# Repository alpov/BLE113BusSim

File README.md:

# BLE113BusSim
Testing framework for Bluegiga BLE113 with MSP432. Provides a method to test Bluetooth Low Energy throughput (Bluegiga BLE113) on MSP432 Launchpad boards (TI MSP-EXP432P401R).

### Required hardware
* CC-Debugger http://www.ti.com/tool/cc-debugger
* MSP-EXP432P401R Launchpads http://www.ti.com/tool/msp-exp432p401r
* Bluegiga BLE113 modules

### Required tools and software
* SmartRF Flash Programmer v1 http://www.ti.com/tool/flash-programmer (v1.12.8)
* Bluegiga Bluetooth Smart Software Stack https://www.silabs.com/products/wireless/bluetooth/bluetooth-smart-modules/Pages/bluegiga-bluetooth-smart-software-stack.aspx (v1.4.2)
* TI Code Composer Studio http://processors.wiki.ti.com/index.php/Download_CCS (v6.2.0.00050)
* MSP432 Driver Library http://www.ti.com/tool/mspdriverlib (v.3.21.00.05)

### Random notes from BLE development
* BLE113 uses UART communication. To achieve the highest possible throughput, use at least 1MBaud.
* Sleep mode needs to be used; otherwise the power consumption is large. Wakeup from sleep is acknowledged with an event, handler needs to wait for it.
* Always wait for response after issuing command to BLE113.
* Connections are very stable after being established, but the connection setup itself is not reliable – gives "Connection Failed to be Established (0x023E)". This is documented in Bluegiga API manual. Solution is to send an acknowledged attribute write after connection; this will either proceed or give 0x023E error. In that case, do a reconnect.
* Support for 8 slaves needs to be enabled in both bgproj (config.xml) and CCS project. Minimum connection interval is 20ms for config of up to 8 slaves; this lowers the maximum achievable throughput.
* To use 20ms connection interval with all 8 slaves, it is necessary to start with longer interval (e.g. 100ms), connect all of them, and then issue an update to 20ms. Otherwise the 7th or 8th slave will connect very late or would not connect at all. Connection interval is not updated right after acknowledgement, it takes several communication intervals.
* With 20ms connection interval, the theoretical maximum write throughput for one node is 20B\*(1/(2\*0.02s))=500B/s. This is because the write packet is limited to 20B and each packet is acknowledged. Large values like 21.1kbit/s from our testing are only achievable with optimal payload distribution – maximum packet length to all slaves simultaneously.
* Nice reading to start with BLE:
  * https://bluegiga.zendesk.com/entries/25053373--REFERENCE-BLE-master-slave-GATT-client-server-and-data-RX-TX-basics
  * https://bluegiga.zendesk.com/entries/22412436--REFERENCE-What-is-the-difference-between-BGScript-BGAPI-and-BGLib
  * https://bluegiga.zendesk.com/entries/23173106--REFERENCE-BLE-module-low-power-and-sleep-modes
  * https://bluegiga.zendesk.com/entries/45890933--REFERENCE-BGAPI-BGLib-Implementation-on-BLE-devices
* Module ble.c provides a basic library for MSP432 to support Bluegiga BLE112/113 modules in UART packet mode. Other support files are from Bluegiga bglib SDK.
* Loading the firmware is possible with CC Debugger. Always use Bluegiga BLE SW Update Tool, not the TI Flash Programmer, as the later one will destroy the license key in BLE113.
* BLE is really suited for very slow communication with negligible throughput. It will perform best for e.g. a sensor, which provides up to 20B of data each ~1 second.

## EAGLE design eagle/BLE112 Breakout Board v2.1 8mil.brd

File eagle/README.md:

# Eagle files for MSP432 breakout boards

* msp432_breakout_ble113 - for BLE113 module
* msp432_breakout_hm10 - for HM-10 module (not tested)
* msp432_breakout_uart - for RS232 and RS485 buses
* ~~msp432_breakout_i2c~~ - for I2C regular and I2C differential buses; warning: the driver footprints are both wrong, need to be fixed before use!
* ~~sf-bluegiga.lbr~~ - library with components; BLE113 is OK, I2C drivers need to be fixed before use!
* BLE112 Breakout Board v2.1 8mil - minor redesign of http://www.inmojo.com/store/jeff-rowberg/item/ble112-bluetooth-low-energy-breakout/ for 8mil DRC; this board with BLE112 can be used as a BLE sniffer, see http://www.ti.com/tool/packet-sniffer

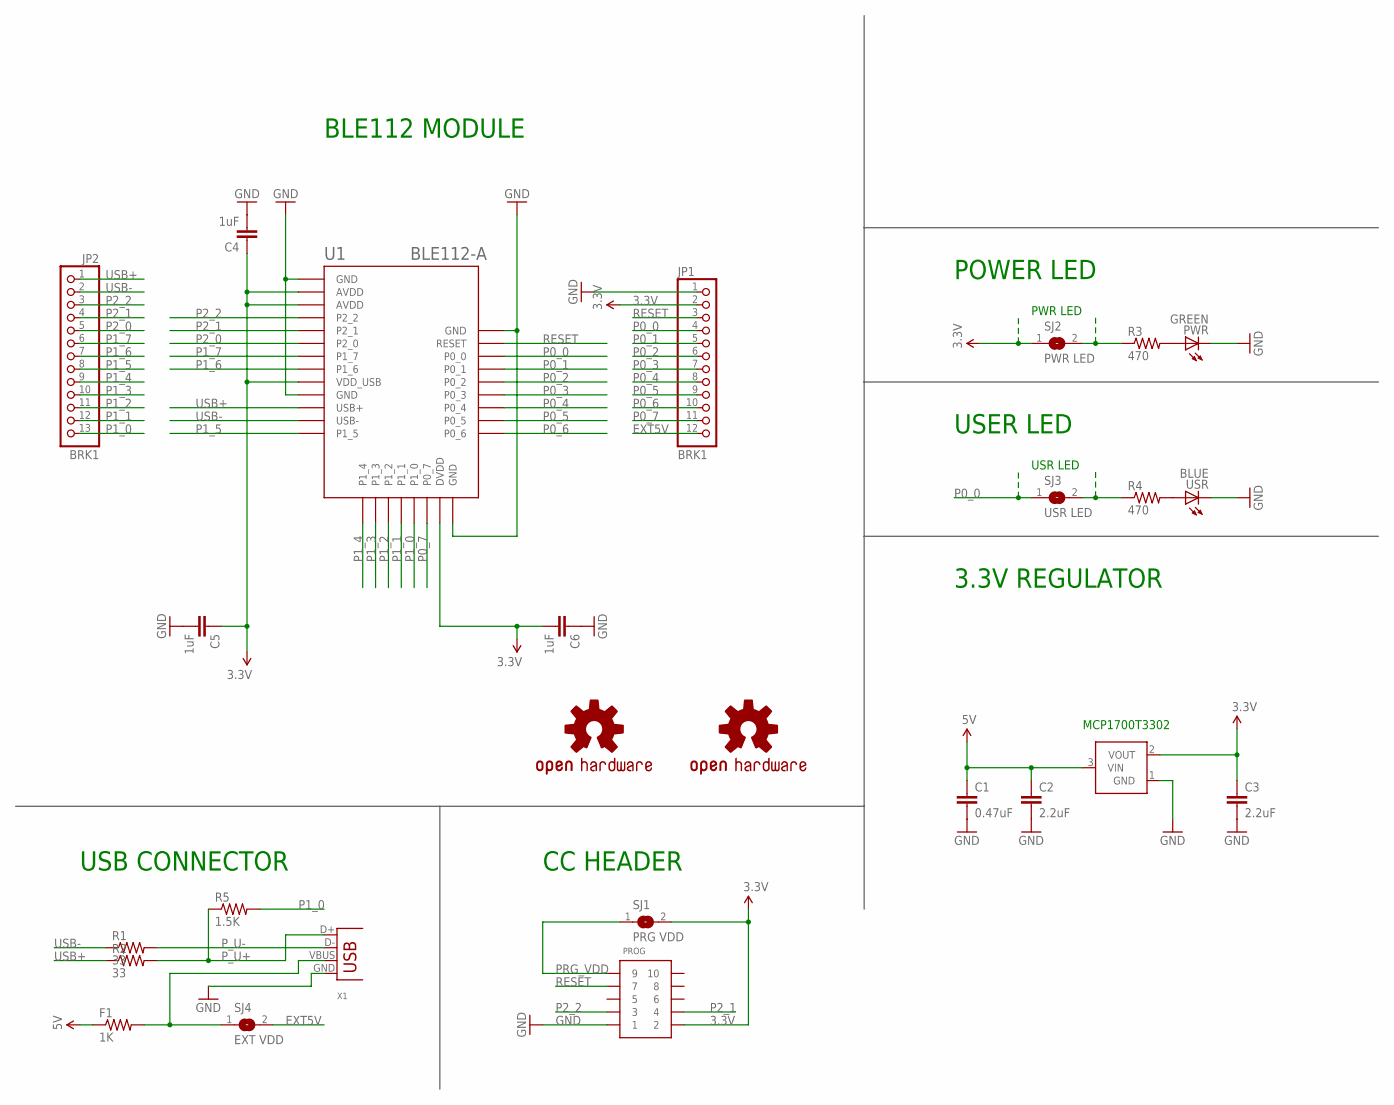
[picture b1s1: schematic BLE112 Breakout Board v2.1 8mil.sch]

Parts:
C1: 0.47uF; 0603-CAP
C2, C3: 2.2uF; 0603-CAP
C4, C5, C6: 1uF; 0603-CAP
F1: 1K; 0805
JP1: BRK1; 1X12
JP2: BRK1; 1X13
OSHW1: OSHW-LOGOL; OSHW-LOGO-L
OSHW2: OSHW-LOGOS; OSHW-LOGO-S
PROG: CONN_5-2-FTSH-V; FTSH-105-DV
PWR: GREEN; CHIPLED_0805
R1, R2: 33; 0603-RES
R3, R4: 470; R0603
R5: 1.5K; 0603-RES
SJ1: PRG VDD; SJ
SJ2: PWR LED; SJ
SJ3: USR LED; SJ
SJ4: EXT VDD; SJ
U1: BLE112-A
U2: MCP1700; SOT23-3
USR: BLUE; CHIPLED_0805
X1: USB-MB-S

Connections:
3.3V: C3.1, C4.1, C5.1, C6.2, JP1.2, PROG.2, SJ1.2, SJ2.1, U1.AVDD1 (AVDD), U1.AVDD2 (AVDD), U1.DVDD, U1.VDD_USB, U2.2 (VOUT)
5V: C1.1, C2.1, F1.1, U2.3 (VIN)
EXT5V: JP1.12, SJ4.2
GND: C1.2, C2.2, C3.2, C4.2, C5.2, C6.1, JP1.1, PROG.1, PWR.C, U1.GND1 (GND), U1.GND2 (GND), U1.GND3 (GND), U1.GND4 (GND), U2.1 (GND), USR.C, X1.GND
unnamed: PWR.A, R3.2
unnamed: R3.1, SJ2.2
unnamed: R4.2, USR.A
unnamed: R4.1, SJ3.2
P0_0: JP1.4, SJ3.1, U1.P0_0
P0_1: JP1.5, U1.P0_1
P0_2: JP1.6, U1.P0_2
P0_3: JP1.7, U1.P0_3
P0_4: JP1.8, U1.P0_4
P0_5: JP1.9, U1.P0_5
P0_6: JP1.10, U1.P0_6
P0_7: JP1.11, U1.P0_7
P1_0: JP2.13, R5.2, U1.P1_0
P1_1: JP2.12, U1.P1_1
P1_2: JP2.11, U1.P1_2
P1_3: JP2.10, U1.P1_3
P1_4: JP2.9, U1.P1_4
P1_5: JP2.8, U1.P1_5
P1_6: JP2.7, U1.P1_6
P1_7: JP2.6, U1.P1_7
P2_0: JP2.5, U1.P2_0
P2_1: JP2.4, PROG.4, U1.P2_1
P2_2: JP2.3, PROG.3, U1.P2_2
PRG_VDD: PROG.9, SJ1.1
P_U+: R2.2, R5.1, X1.D+
P_U-: R1.2, X1.D-
RESET: JP1.3, PROG.7, U1.RESET
USB+: JP2.1, R2.1, U1.USB+
USB-: JP2.2, R1.1, U1.USB-
VBUS: F1.2, SJ4.1, X1.VBUS

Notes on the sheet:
PWR LED
USR LED
POWER LED
USER LED
USB CONNECTOR
CC HEADER
BLE112 MODULE
3.3V REGULATOR
MCP1700T3302

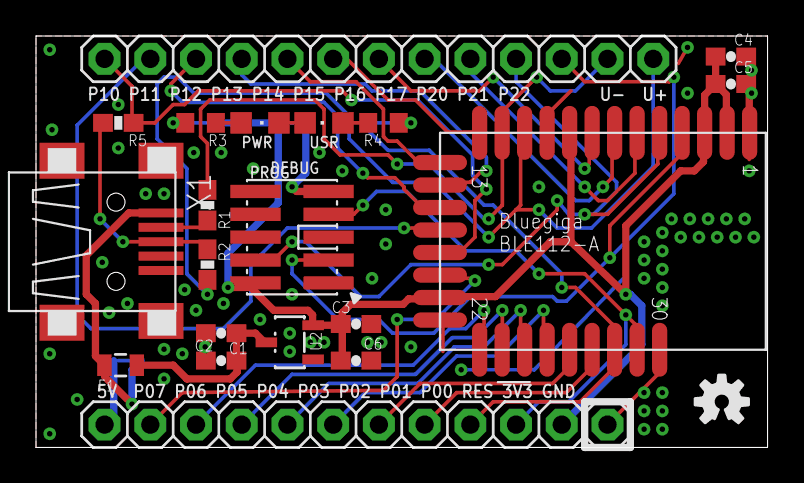
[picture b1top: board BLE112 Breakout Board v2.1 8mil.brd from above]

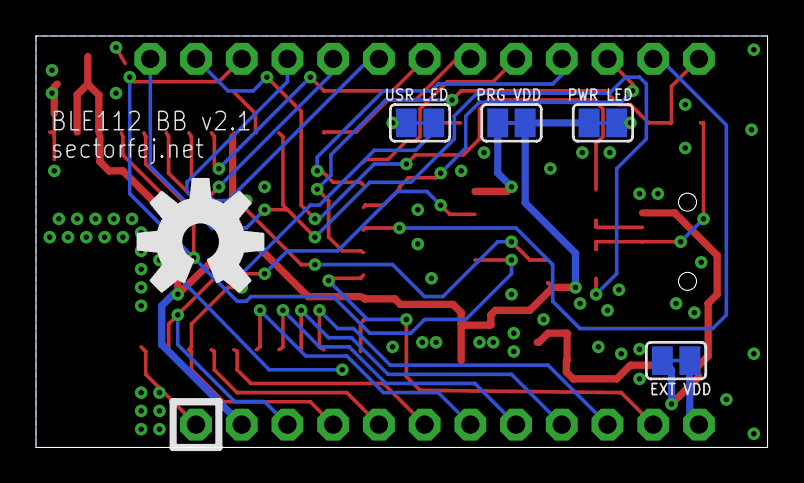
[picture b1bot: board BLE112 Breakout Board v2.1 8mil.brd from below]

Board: 2 copper layers, 40.6 x 22.9 mm, 26 parts (5 on the bottom side), 34 nets.

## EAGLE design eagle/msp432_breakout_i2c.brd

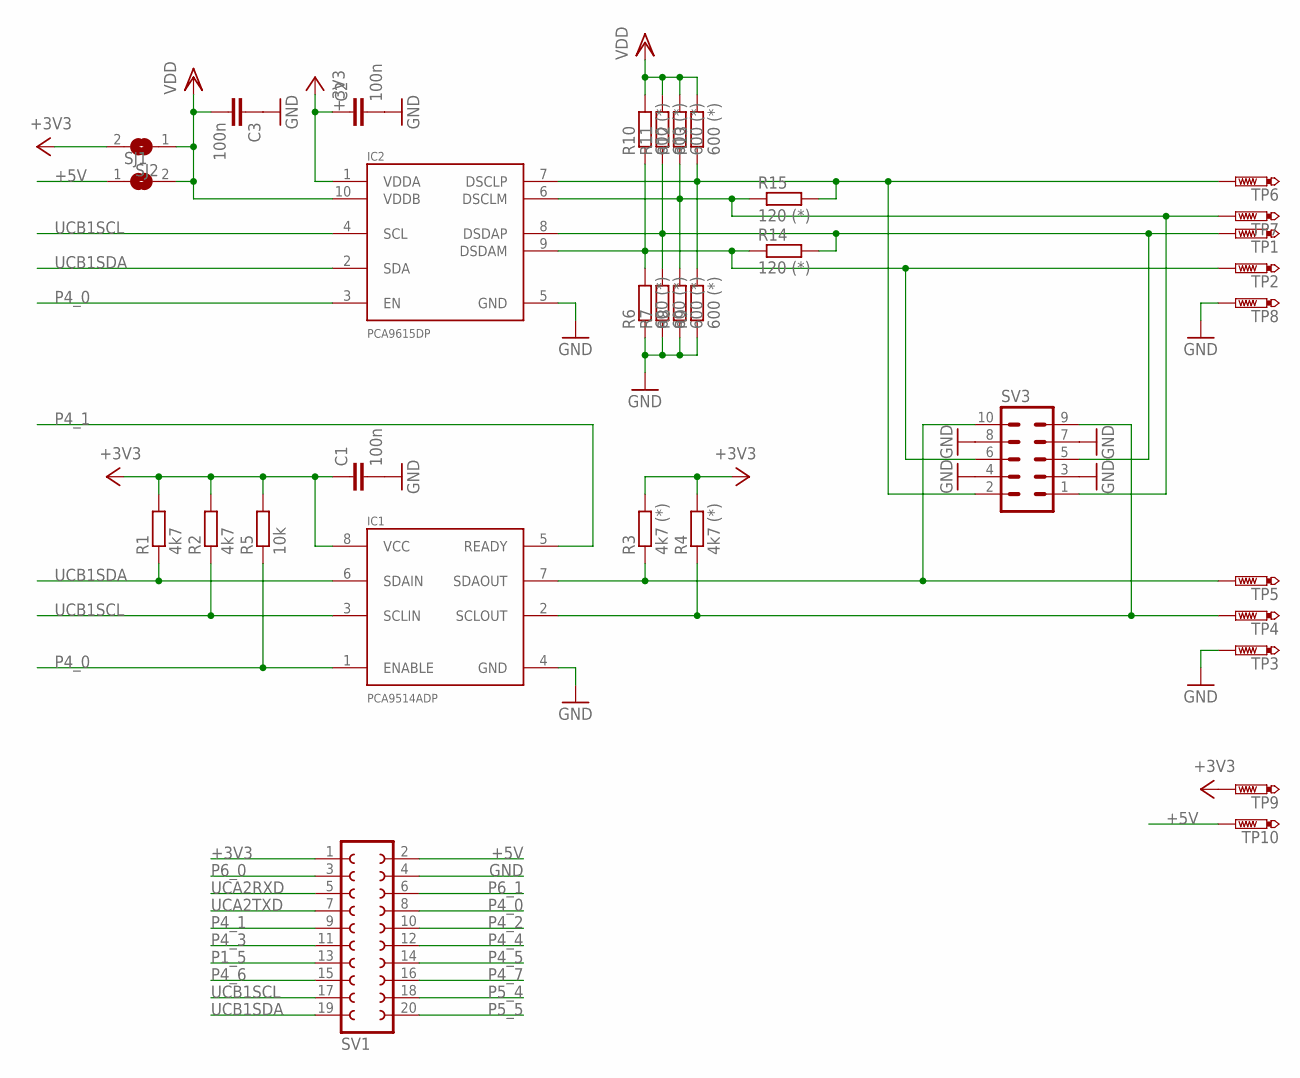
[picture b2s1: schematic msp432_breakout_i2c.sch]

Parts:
C1, C2, C3: 100n; C0603
IC1: PCA9514ADP; TSSOP8
IC2: PCA9615DP; TSSOP10
R1, R2: 4k7; R0603
R3, R4: 4k7 (*); R0603
R5: 10k; R0603
R6, R7, R8, R9, R10, R11, R12, R13: 600 (*); R0603
R14, R15: 120 (*); R0603
SJ1, SJ2: SJ
SV1: FE10-2
SV3: ML10
TP1: DSDAP; P1-17
TP2: DSDAM; P1-17
TP3, TP8: GND; P1-17
TP4: SCLOUT; P1-17
TP5: SDAOUT; P1-17
TP6: DSCLP; P1-17
TP7: DSCLM; P1-17
TP9: 3V3; P1-17
TP10: 5V; P1-17

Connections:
+3V3: C1.1, C2.1, IC1.8 (VCC), IC2.1 (VDDA), R1.2, R2.2, R3.2, R4.2, R5.2, SJ2.2, SV1.1, TP9.TP
+5V: SJ1.1, SV1.2, TP10.TP
GND: C1.2, C2.2, C3.1, IC1.4 (GND), IC2.5 (GND), R6.1, R7.1, R8.1, R9.1, SV1.4, SV3.3, SV3.4, SV3.7, SV3.8, TP3.TP, TP8.TP
P1_5: SV1.13
P4_0: IC1.1 (ENABLE), IC2.3 (EN), R5.1, SV1.8
P4_1: IC1.5 (READY), SV1.9
P4_2: SV1.10
P4_3: SV1.11
P4_4: SV1.12
P4_5: SV1.14
P4_6: SV1.15
P4_7: SV1.16
P5_4: SV1.18
P5_5: SV1.20
P6_0: SV1.3
P6_1: SV1.6
SCL: IC1.2 (SCLOUT), R4.1, SV3.9, TP4.TP
SCLM: IC2.6 (DSCLM), R8.2, R12.1, R15.1, SV3.1, TP7.TP
SCLP: IC2.7 (DSCLP), R9.2, R13.1, R15.2, SV3.2, TP6.TP
SDA: IC1.7 (SDAOUT), R3.1, SV3.10, TP5.TP
SDAM: IC2.9 (DSDAM), R6.2, R10.1, R14.1, SV3.6, TP2.TP
SDAP: IC2.8 (DSDAP), R7.2, R11.1, R14.2, SV3.5, TP1.TP
UCA2RXD: SV1.5
UCA2TXD: SV1.7
UCB1SCL: IC1.3 (SCLIN), IC2.4 (SCL), R2.1, SV1.17
UCB1SDA: IC1.6 (SDAIN), IC2.2 (SDA), R1.1, SV1.19
VDD: C3.2, IC2.10 (VDDB), R10.2, R11.2, R12.2, R13.2, SJ1.2, SJ2.1

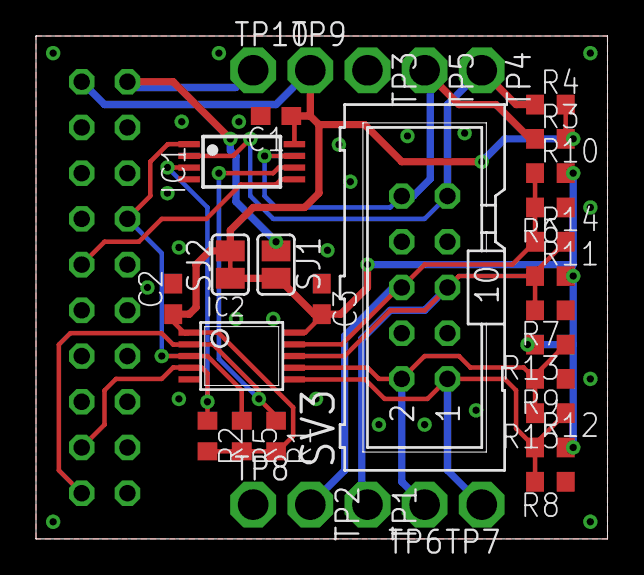
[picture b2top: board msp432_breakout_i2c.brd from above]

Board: 2 copper layers, 31.8 x 27.9 mm, 34 parts (1 on the bottom side), 14 nets.

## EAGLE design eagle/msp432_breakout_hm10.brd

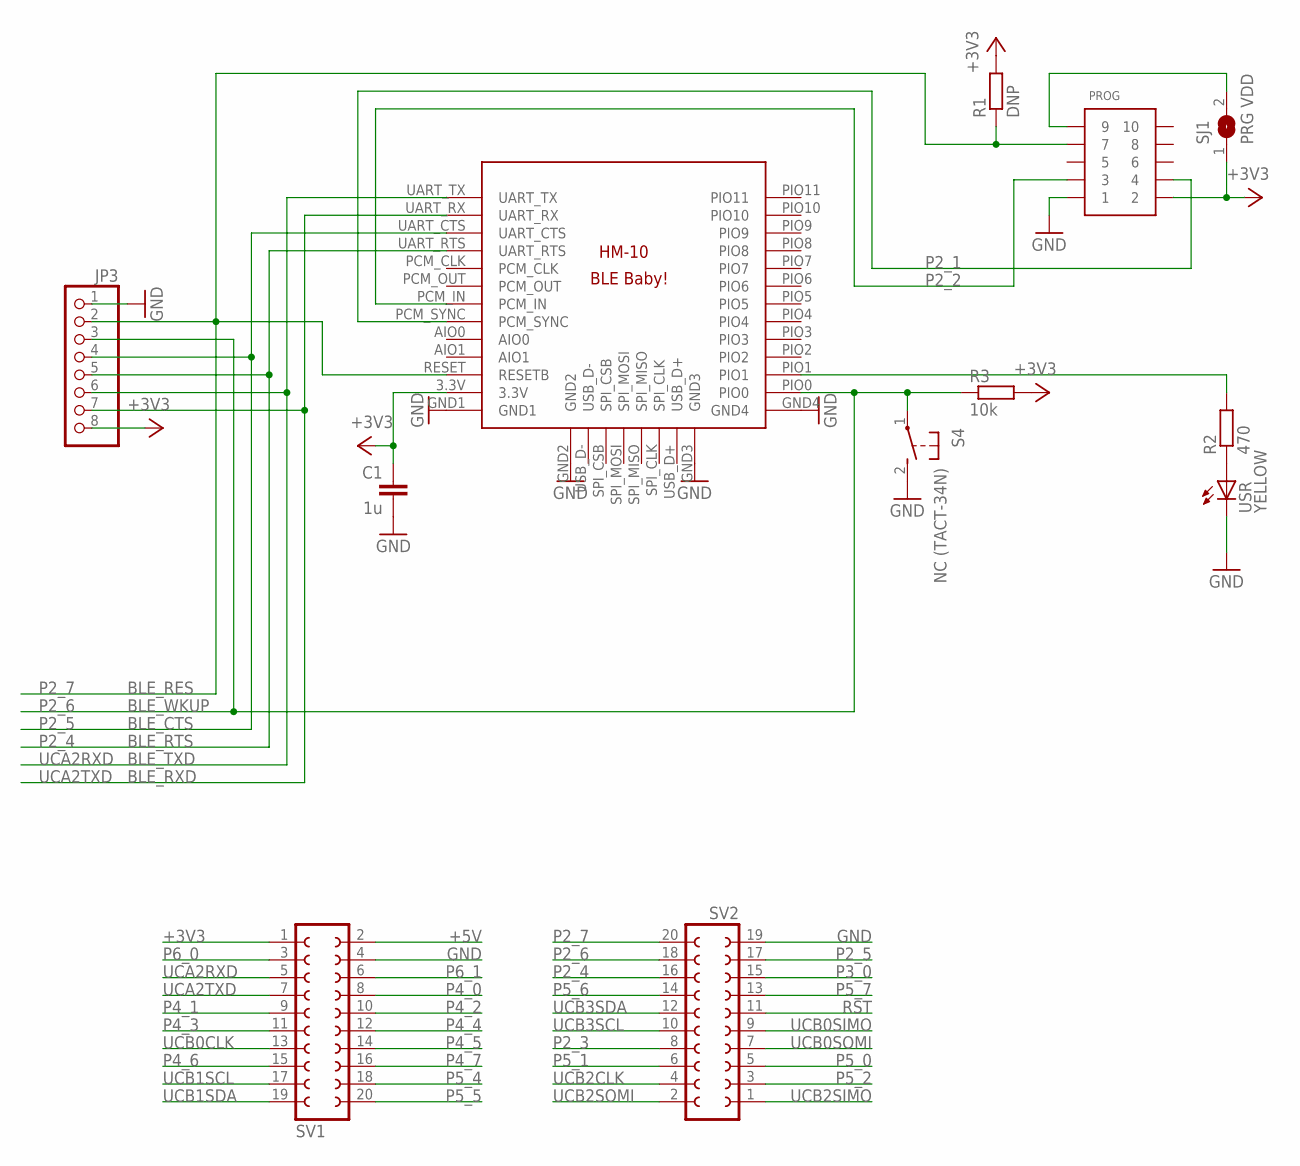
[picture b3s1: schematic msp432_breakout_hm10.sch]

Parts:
C1: 1u; C0603
JP3: PINHD-1X8; 1X08
PROG: CONN_5-2-FTSH-V; FTSH-105-DV
R1: DNP; R0603
R2: 470; R0603
R3: 10k; R0603
S4: NC (TACT-34N); TACT-34N
SJ1: PRG VDD; SJ
SV1, SV2: FE10-2
U$1: BLE-HM-10
USR: YELLOW; CHIPLED_0805

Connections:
+3V3: C1.1, JP3.8, PROG.2, R1.2, R3.2, SJ1.1, SV1.1, U$1.3.3V
+5V: SV1.2
GND: C1.2, JP3.1, PROG.1, S4.2 (S), SV1.4, SV2.19, U$1.GND1, U$1.GND2, U$1.GND3, U$1.GND4, USR.C
unnamed: R2.1, USR.A
unnamed: R2.2, U$1.PIO1
unnamed: PROG.9, SJ1.2
P2_1: PROG.4, U$1.PCM_SYNC
P2_2: PROG.3, U$1.PCM_IN
P2_3: SV2.8
P2_4: JP3.5, SV2.16, U$1.UART_RTS
P2_5: JP3.4, SV2.17, U$1.UART_CTS
P2_6: JP3.3, R3.1, S4.1, SV2.18, U$1.PIO0
P2_7: JP3.2, PROG.7, R1.1, SV2.20, U$1.RESET (RESETB)
P3_0: SV2.15
P4_0: SV1.8
P4_1: SV1.9
P4_2: SV1.10
P4_3: SV1.11
P4_4: SV1.12
P4_5: SV1.14
P4_6: SV1.15
P4_7: SV1.16
P5_0: SV2.5
P5_1: SV2.6
P5_2: SV2.3
P5_4: SV1.18
P5_5: SV1.20
P5_6: SV2.14
P5_7: SV2.13
P6_0: SV1.3
P6_1: SV1.6
RST: SV2.11
UCA2RXD: JP3.6, SV1.5, U$1.UART_TX
UCA2TXD: JP3.7, SV1.7, U$1.UART_RX
UCB0CLK: SV1.13
UCB0SIMO: SV2.9
UCB0SOMI: SV2.7
UCB1SCL: SV1.17
UCB1SDA: SV1.19
UCB2CLK: SV2.4
UCB2SIMO: SV2.1
UCB2SOMI: SV2.2
UCB3SCL: SV2.10
UCB3SDA: SV2.12

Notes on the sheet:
BLE_RES
BLE_WKUP
BLE_CTS
BLE_RTS
BLE_RXD
BLE_TXD

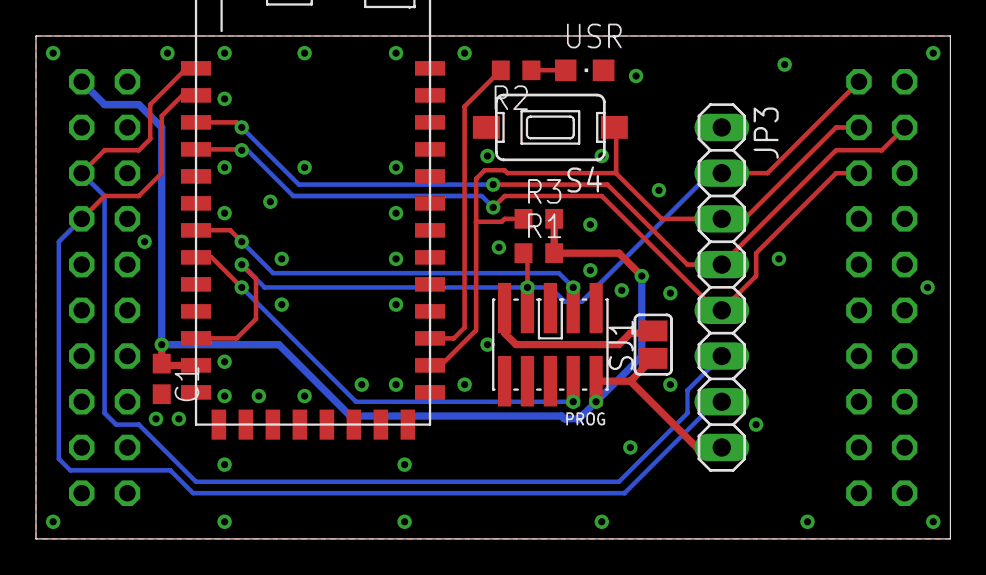
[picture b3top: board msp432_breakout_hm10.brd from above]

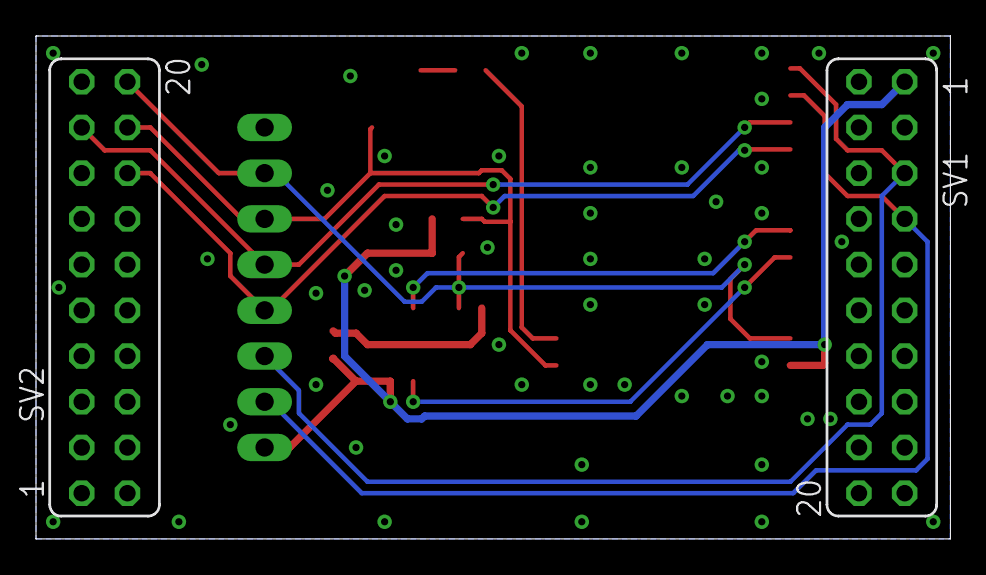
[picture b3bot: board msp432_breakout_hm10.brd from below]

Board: 2 copper layers, 50.8 x 27.9 mm, 12 parts (2 on the bottom side), 13 nets.

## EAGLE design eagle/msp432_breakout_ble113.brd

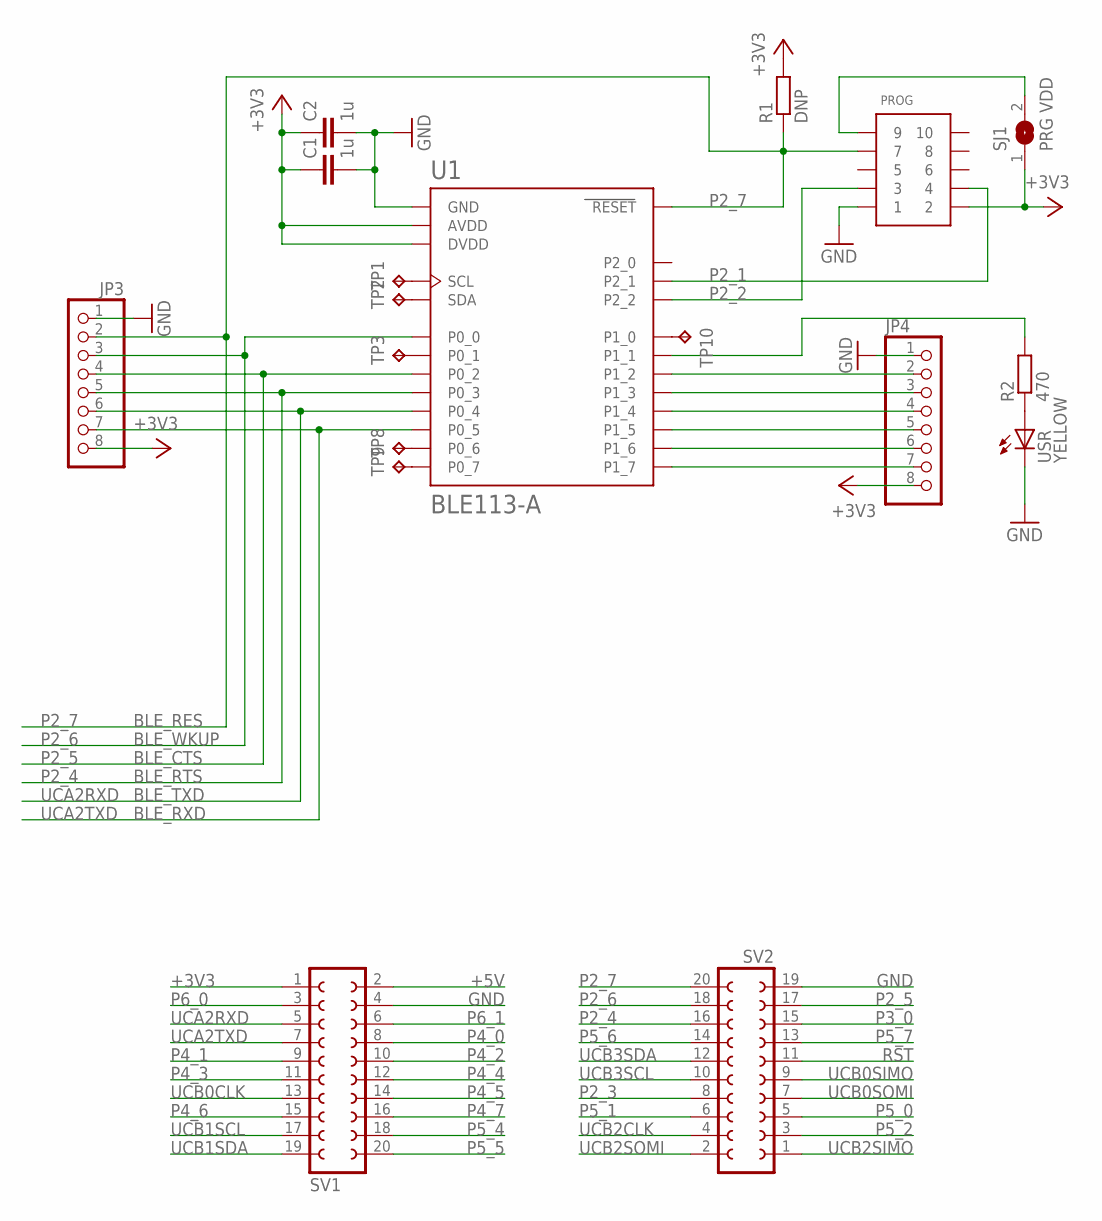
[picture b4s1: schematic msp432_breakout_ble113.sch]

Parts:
C1, C2: 1u; C0603
JP3, JP4: PINHD-1X8; 1X08
PROG: CONN_5-2-FTSH-V; FTSH-105-DV
R1: DNP; R0603
R2: 470; R0603
SJ1: PRG VDD; SJ
SV1, SV2: FE10-2
TP1, TP2, TP3, TP8, TP9, TP10: TPB1,27; B1,27
U1: BLE113-A
USR: YELLOW; CHIPLED_0805

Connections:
+3V3: C1.1, C2.1, JP3.8, JP4.8, PROG.2, R1.2, SJ1.1, SV1.1, U1.AVDD, U1.DVDD
+5V: SV1.2
GND: C1.2, C2.2, JP3.1, JP4.1, PROG.1, SV1.4, SV2.19, U1.GND, U1.GND@2 (GND), U1.GND@3 (GND), U1.GND@4 (GND), U1.GND@5 (GND), U1.GND@6 (GND), U1.GND@7 (GND), U1.GND@8 (GND), U1.GND@9 (GND), U1.GND@10 (GND), USR.C
unnamed: TP3.TP, U1.P0_1
unnamed: R2.1, USR.A
unnamed: JP4.6, U1.P1_6
unnamed: JP4.7, U1.P1_7
unnamed: R2.2, U1.P1_1
unnamed: TP8.TP, U1.P0_6
unnamed: TP9.TP, U1.P0_7
unnamed: PROG.9, SJ1.2
unnamed: TP1.TP, U1.SCL
unnamed: TP2.TP, U1.SDA
P1_0: TP10.TP, U1.P1_0
P1_2: JP4.2, U1.P1_2
P1_3: JP4.3, U1.P1_3
P1_4: JP4.4, U1.P1_4
P1_5: JP4.5, U1.P1_5
P2_1: PROG.4, U1.P2_1
P2_2: PROG.3, U1.P2_2
P2_3: SV2.8
P2_4: JP3.5, SV2.16, U1.P0_3
P2_5: JP3.4, SV2.17, U1.P0_2
P2_6: JP3.3, SV2.18, U1.P0_0
P2_7: JP3.2, PROG.7, R1.1, SV2.20, U1.RESET
P3_0: SV2.15
P4_0: SV1.8
P4_1: SV1.9
P4_2: SV1.10
P4_3: SV1.11
P4_4: SV1.12
P4_5: SV1.14
P4_6: SV1.15
P4_7: SV1.16
P5_0: SV2.5
P5_1: SV2.6
P5_2: SV2.3
P5_4: SV1.18
P5_5: SV1.20
P5_6: SV2.14
P5_7: SV2.13
P6_0: SV1.3
P6_1: SV1.6
RST: SV2.11
UCA2RXD: JP3.6, SV1.5, U1.P0_4
UCA2TXD: JP3.7, SV1.7, U1.P0_5
UCB0CLK: SV1.13
UCB0SIMO: SV2.9
UCB0SOMI: SV2.7
UCB1SCL: SV1.17
UCB1SDA: SV1.19
UCB2CLK: SV2.4
UCB2SIMO: SV2.1
UCB2SOMI: SV2.2
UCB3SCL: SV2.10
UCB3SDA: SV2.12

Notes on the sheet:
BLE_RES
BLE_WKUP
BLE_CTS
BLE_RTS
BLE_RXD
BLE_TXD

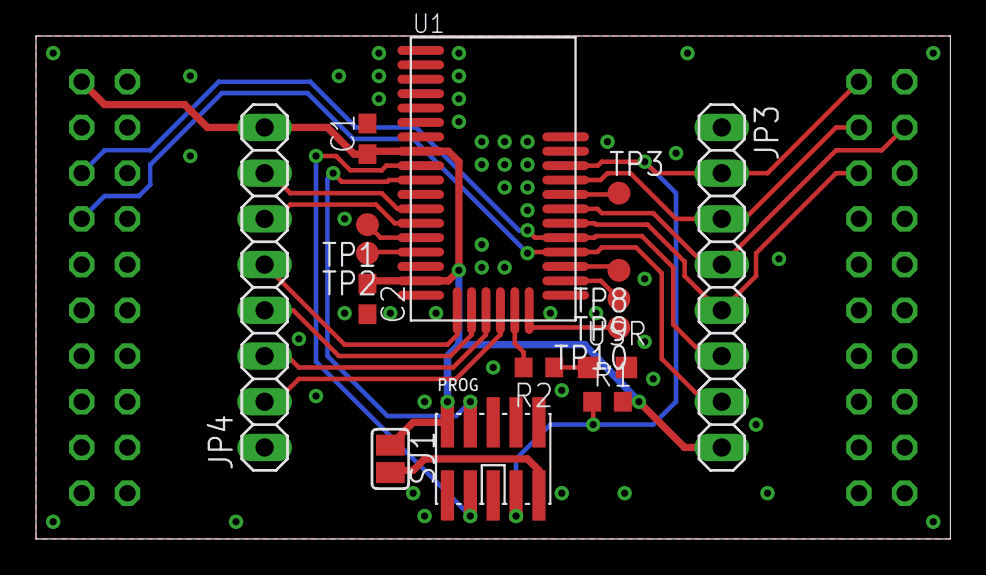
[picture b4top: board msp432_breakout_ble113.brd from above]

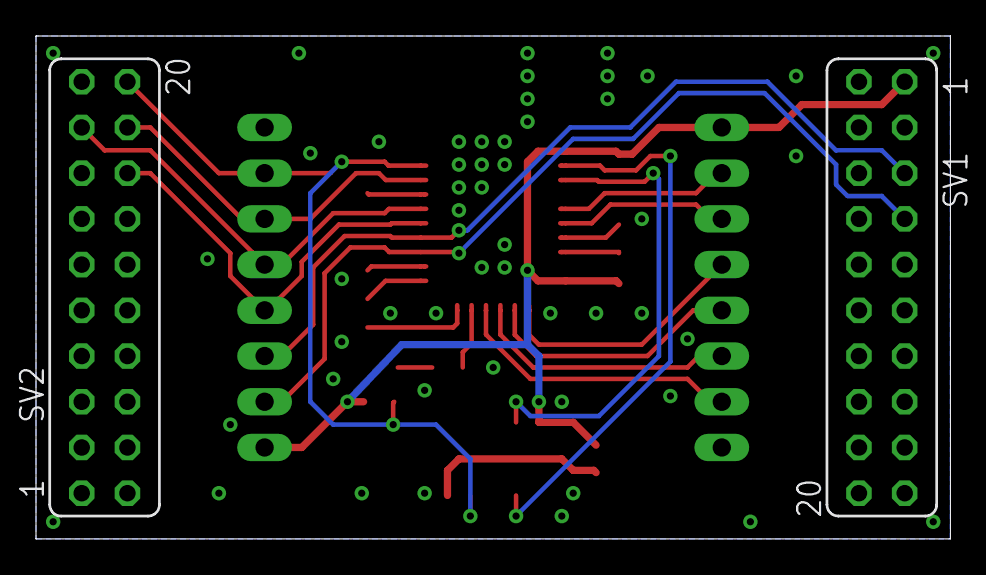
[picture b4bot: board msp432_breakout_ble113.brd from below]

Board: 2 copper layers, 50.8 x 27.9 mm, 18 parts (2 on the bottom side), 25 nets.

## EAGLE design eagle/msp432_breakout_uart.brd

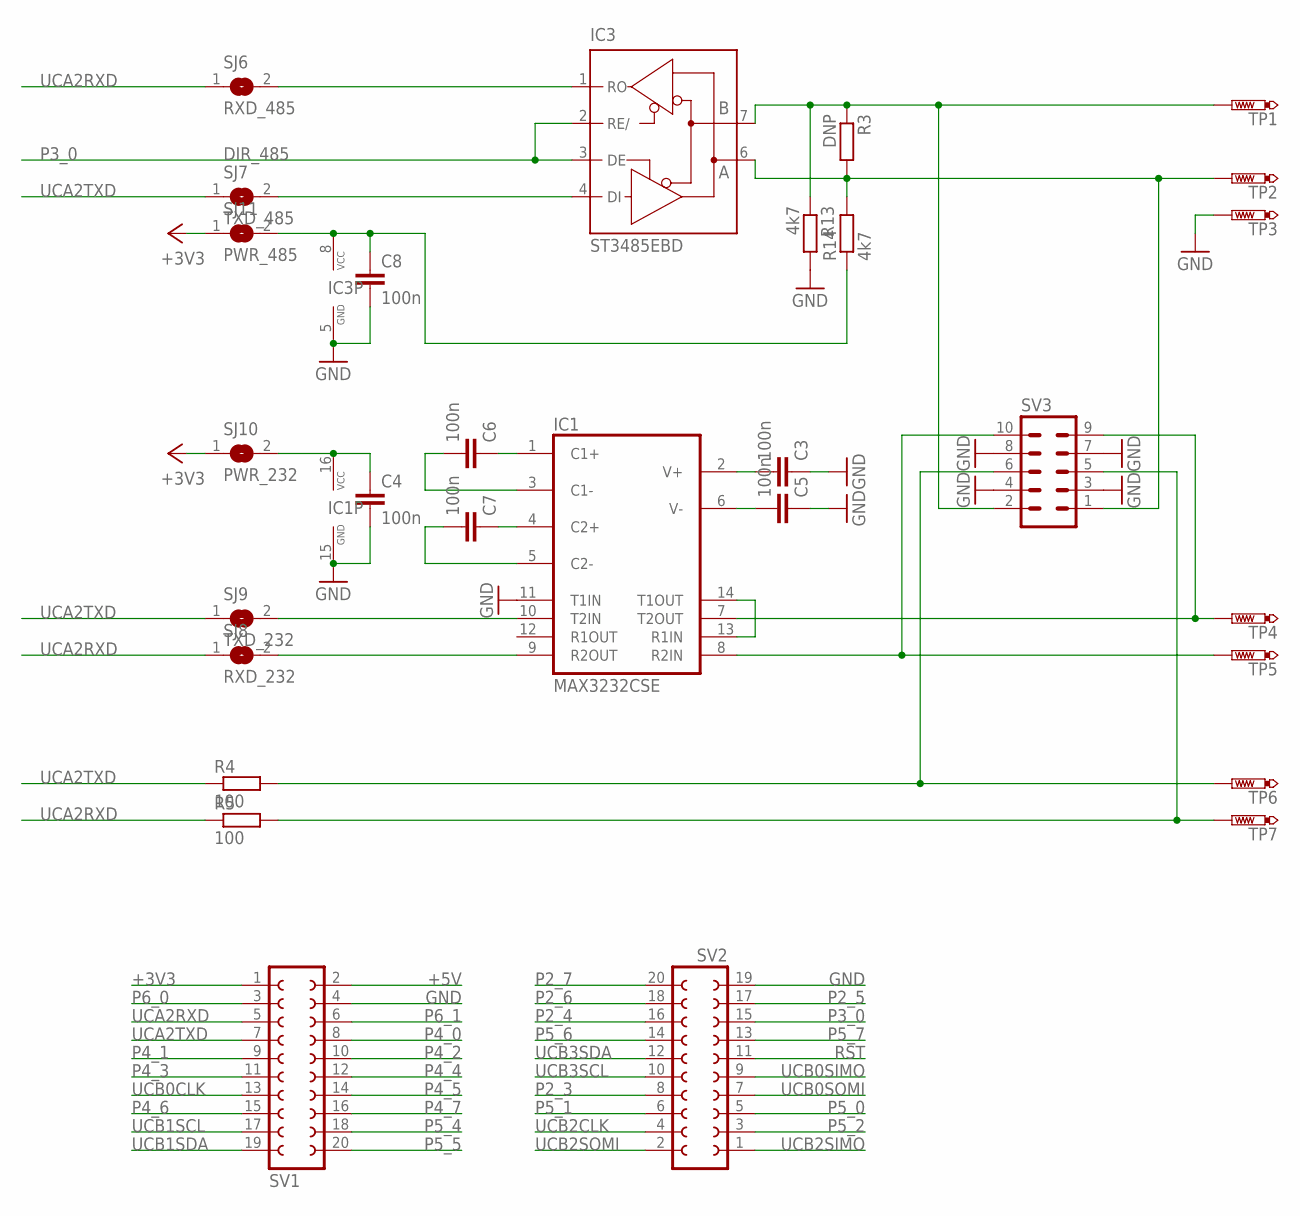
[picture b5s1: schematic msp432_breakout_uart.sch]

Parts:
C3, C4, C5, C6, C7, C8: 100n; C0603
IC1: MAX3232CSE; SO16
IC3: ST3485EBD; SO08
R3: DNP; R0603
R4, R5: 100; R0603
R13, R14: 4k7; R0603
SJ6: RXD_485; SJ
SJ7: TXD_485; SJ
SJ8: RXD_232; SJ
SJ9: TXD_232; SJ
SJ10: PWR_232; SJ
SJ11: PWR_485; SJ
SV1, SV2: FE10-2
SV3: ML10
TP1, TP2, TP3, TP4, TP5, TP6, TP7: PTR1PAD1-20; P1-20

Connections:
+3V3: SJ10.1, SJ11.1, SV1.1
+5V: SV1.2
CA: IC3.6 (A), R3.2, R14.2, SV3.1, TP2.TP
CB: IC3.7 (B), R3.1, R13.1, SV3.2, TP1.TP
GND: C3.1, C4.2, C5.1, C8.2, IC1.11 (T1IN), IC1.15 (GND), IC3.5 (GND), R13.2, SV1.4, SV2.19, SV3.3, SV3.4, SV3.7, SV3.8, TP3.TP
unnamed: IC1.8 (R2IN), SV3.10, TP5.TP
unnamed: R5.2, SV3.5, TP7.TP
unnamed: R4.2, SV3.6, TP6.TP
unnamed: IC1.7 (T2OUT), SV3.9, TP4.TP
unnamed: C5.2, IC1.6 (V-)
unnamed: C3.2, IC1.2 (V+)
unnamed: C6.1, IC1.1 (C1+)
unnamed: C6.2, IC1.3 (C1-)
unnamed: C7.1, IC1.4 (C2+)
unnamed: C7.2, IC1.5 (C2-)
unnamed: IC1.13 (R1IN), IC1.14 (T1OUT)
unnamed: IC1.10 (T2IN), SJ9.2
unnamed: IC1.9 (R2OUT), SJ8.2
unnamed: IC3.1 (RO), SJ6.2
unnamed: IC3.4 (DI), SJ7.2
unnamed: C4.1, IC1.16 (VCC), SJ10.2
unnamed: C8.1, IC3.8 (VCC), R14.1, SJ11.2
P2_3: SV2.8
P2_4: SV2.16
P2_5: SV2.17
P2_6: SV2.18
P2_7: SV2.20
P3_0: IC3.2 (RE/), IC3.3 (DE), SV2.15
P4_0: SV1.8
P4_1: SV1.9
P4_2: SV1.10
P4_3: SV1.11
P4_4: SV1.12
P4_5: SV1.14
P4_6: SV1.15
P4_7: SV1.16
P5_0: SV2.5
P5_1: SV2.6
P5_2: SV2.3
P5_4: SV1.18
P5_5: SV1.20
P5_6: SV2.14
P5_7: SV2.13
P6_0: SV1.3
P6_1: SV1.6
RST: SV2.11
UCA2RXD: R5.1, SJ6.1, SJ8.1, SV1.5
UCA2TXD: R4.1, SJ7.1, SJ9.1, SV1.7
UCB0CLK: SV1.13
UCB0SIMO: SV2.9
UCB0SOMI: SV2.7
UCB1SCL: SV1.17
UCB1SDA: SV1.19
UCB2CLK: SV2.4
UCB2SIMO: SV2.1
UCB2SOMI: SV2.2
UCB3SCL: SV2.10
UCB3SDA: SV2.12

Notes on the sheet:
DIR_485

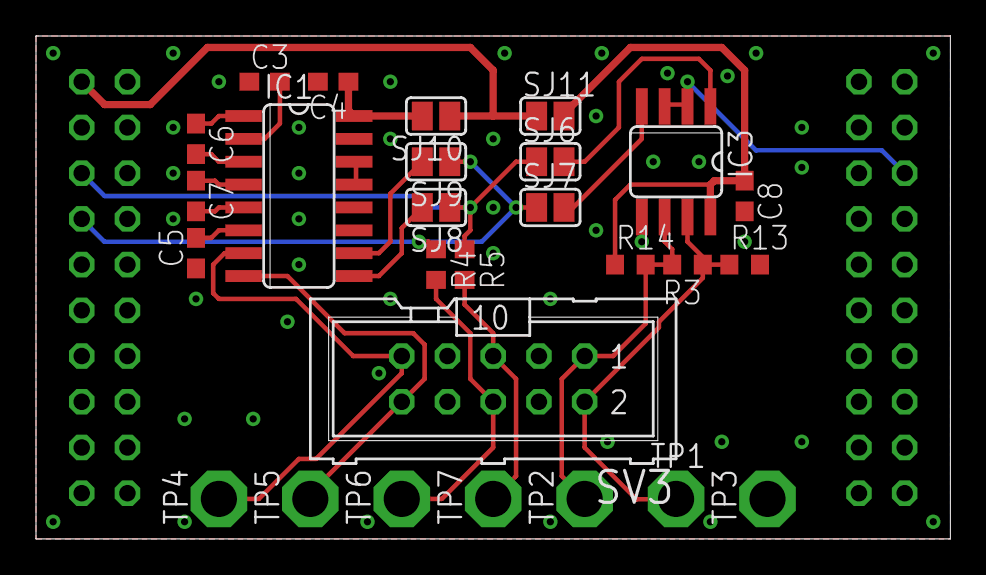
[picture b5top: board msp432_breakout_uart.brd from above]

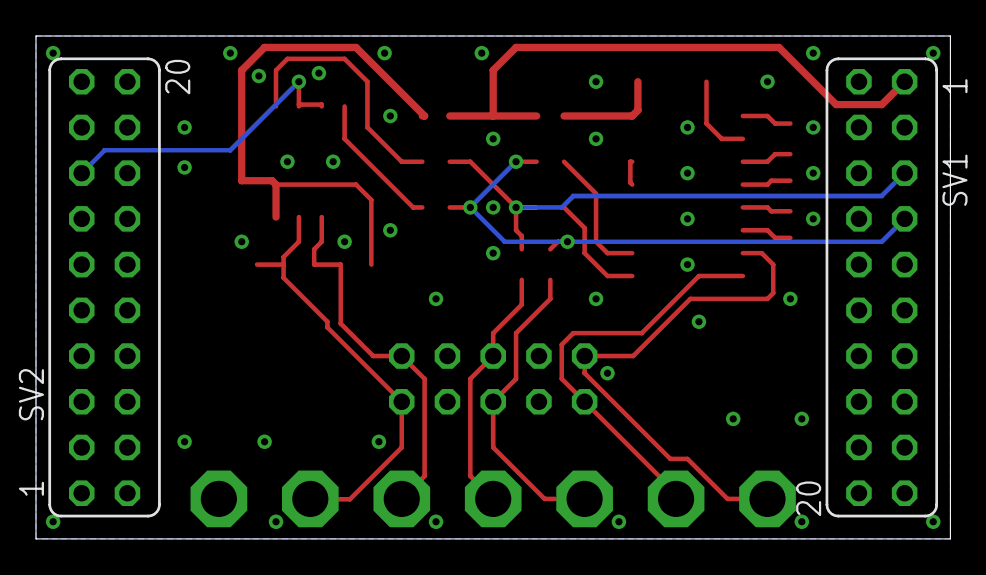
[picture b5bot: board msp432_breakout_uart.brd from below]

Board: 2 copper layers, 50.8 x 27.9 mm, 29 parts (2 on the bottom side), 24 nets.

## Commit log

2016-10-27 BLE113BusSim project import
2016-10-27 Added Eagle files
2016-10-27 More Eagle files

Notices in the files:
parts and their libraries:
SparkFun: Licensing: CC v3.0 Share-Alike You are welcome to use this library for commercial purposes.
